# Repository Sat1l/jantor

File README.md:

# Jantor

Jantor is a split-ergo-keyboard which derives its features from other ergo keebs: [Jian](https://github.com/KGOH/Jian-Info) (extra pinky keys), [Nijuni](https://github.com/krikun98/nijuni) (copied controller footprint) and [Cantor](https://github.com/diepala/cantor) (diodeless design with a Blackpill)

## Features
* Diodeless
* <30 min assembly time
* Combined MX and Hotswap footprints
* Fully simmetrical PCB
* Two ways to connect the halves: jumper wires and TRRS

## Case

Current case design is designed to be cut out of EVA foam on a CNC laser and stacked together using EVA melting chemicals or instant glue.

Case .svg files are stored in the `case` folder, with folder `case production` having production optimised versions which have more pieces per sheet.

Raw case files are stored in `case kicad` folder in kicad project file format.

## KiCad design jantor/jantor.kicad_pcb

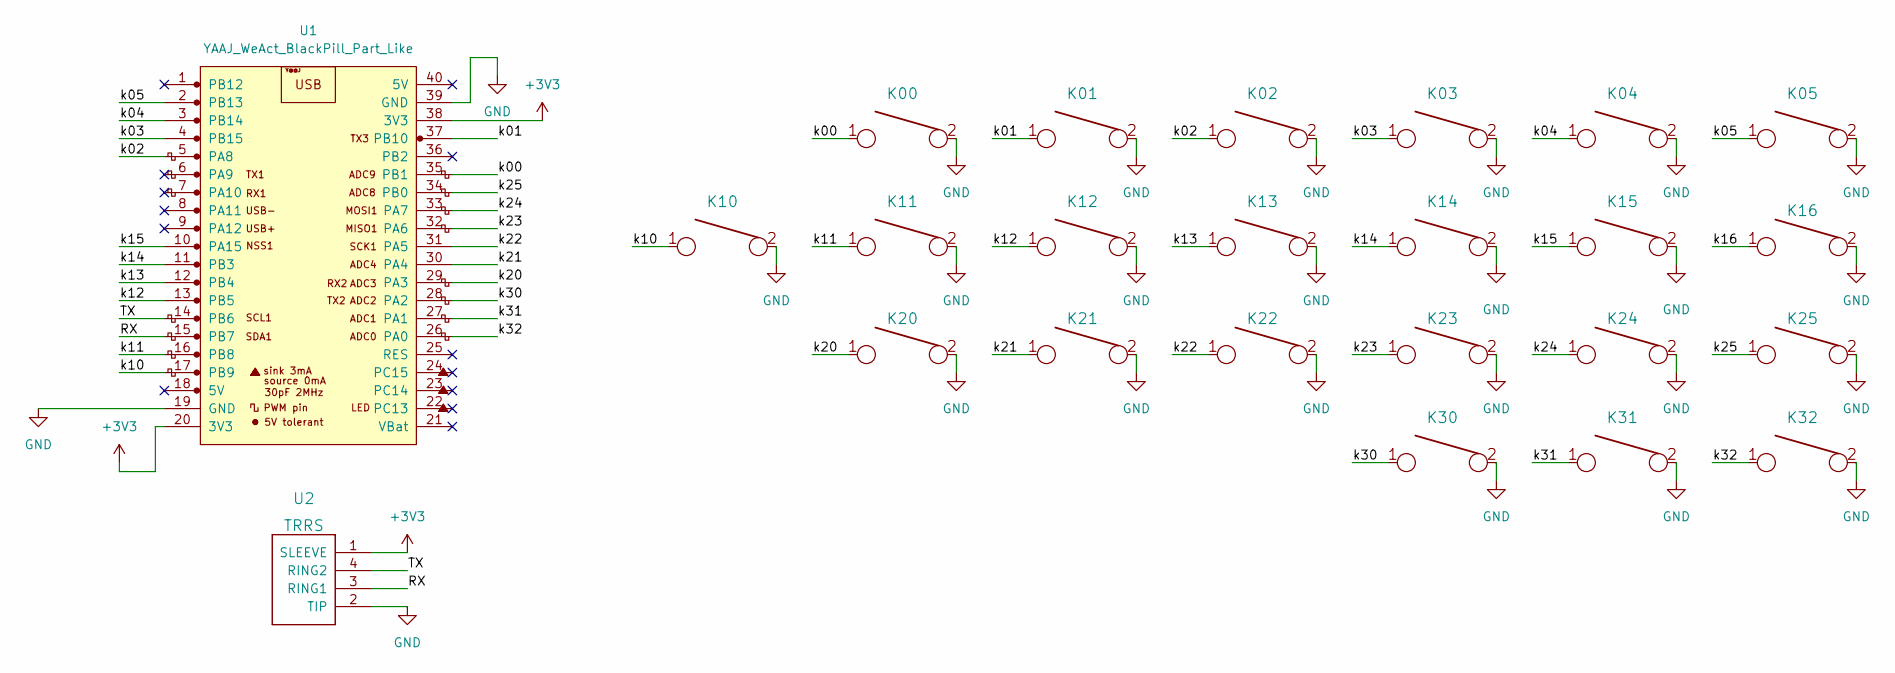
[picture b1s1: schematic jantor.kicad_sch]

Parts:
K00, K01, K02, K03, K04, K05, K10, K11, K12, K13, K14, K15, K16, K20, K21, K22, K23, K24, K25, K30, K31: KEYSW; MXOnly-1U-Hotswap-Optional-Reversible-19mm
K32: KEYSW; MXOnly-1.5U-Hotswap-Optional-Reversible-19mm
U1: YAAJ_WeAct_BlackPill_Part_Like; YAAJ_WeAct_BlackPill_2
U2: TRRS; TRRS-PJ-320A-Reversible

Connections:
+3V3: U1.20 (3V3), U1.38 (3V3), U2.1 (SLEEVE)
/RX: U1.15 (PB7), U2.3 (RING1)
/TX: U1.14 (PB6), U2.4 (RING2)
/k00: K00.1, U1.35 (PB1)
/k01: K01.1, U1.6 (PA9), U1.37 (PB10)
/k02: K02.1, U1.5 (PA8)
/k03: K03.1, U1.4 (PB15)
/k04: K04.1, U1.3 (PB14)
/k05: K05.1, U1.2 (PB13)
/k10: K10.1, U1.17 (PB9)
/k11: K11.1, U1.16 (PB8)
/k12: K12.1, U1.13 (PB5)
/k13: K13.1, U1.12 (PB4)
/k14: K14.1, U1.11 (PB3)
/k15: K15.1, U1.10 (PA15)
/k16: K16.1, U1.9 (PA12)
/k20: K20.1, U1.29 (PA3)
/k21: K21.1, U1.30 (PA4)
/k22: K22.1, U1.31 (PA5)
/k23: K23.1, U1.32 (PA6)
/k24: K24.1, U1.33 (PA7)
/k25: K25.1, U1.34 (PB0)
/k30: K30.1, U1.28 (PA2)
/k31: K31.1, U1.27 (PA1)
/k32: K32.1, U1.26 (PA0)
GND: K00.2, K01.2, K02.2, K03.2, K04.2, K05.2, K10.2, K11.2, K12.2, K13.2, K14.2, K15.2, K16.2, K20.2, K21.2, K22.2, K23.2, K24.2, K25.2, K30.2, K31.2, K32.2, U1.19 (GND), U1.39 (GND), U2.2 (TIP)

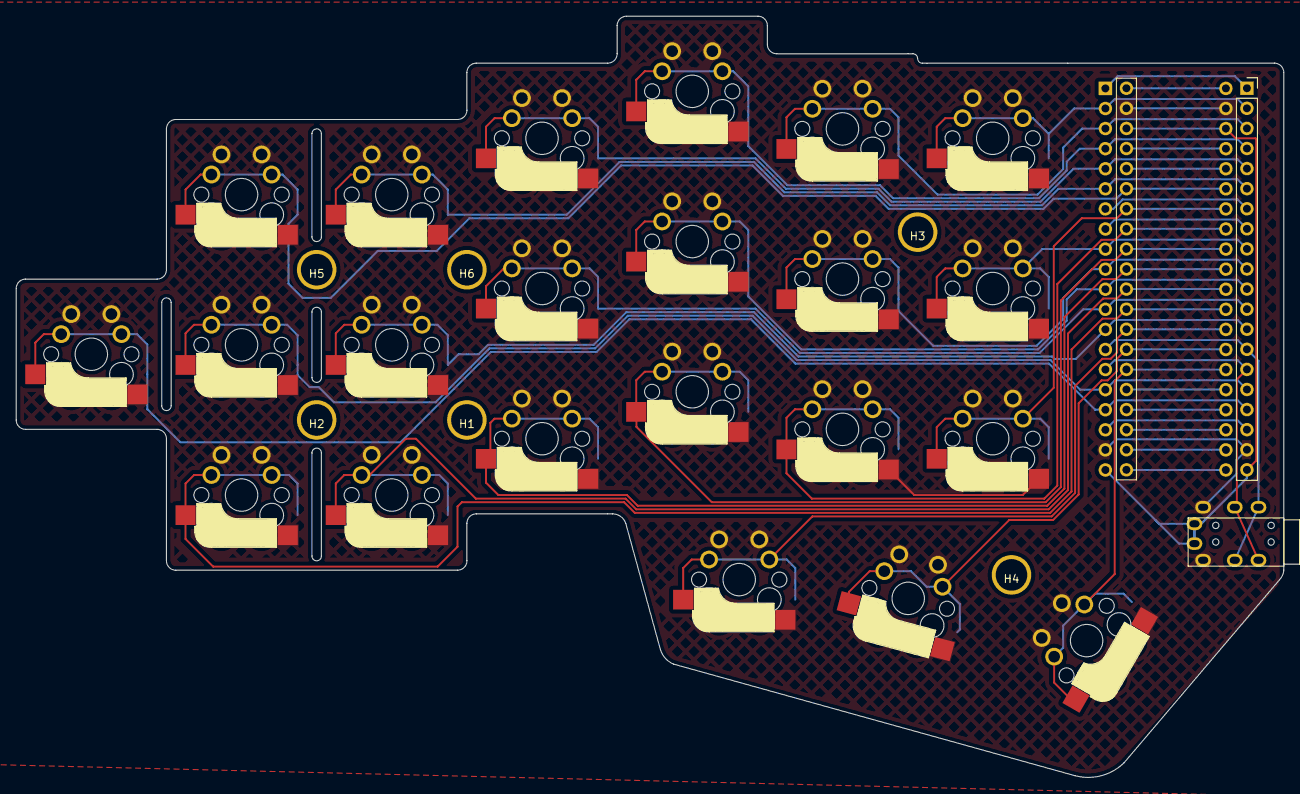
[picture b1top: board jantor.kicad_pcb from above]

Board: 2 copper layers, 160.3 x 96.3 mm, 34 parts (0 on the bottom side), 26 nets.

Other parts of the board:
B1, B3, B4: breakaway; breakaway .75U (for 19mm net)
B2: breakaway; breakaway .5U (for 19mm net)
H1, H2, H3, H4, H5, H6: MountingHole; M2_Hole_TH_Outside

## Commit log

2022-08-20 initial commit
    no wiring and edges
2022-08-21 release
2022-12-30 what i did like whaaaa
2023-06-30 proto v0.?
    Completely new pcb and a new foam case. I'm currently typing this on an assembled board.
2023-07-10 cleanup
2023-07-13 added pictures
2024-04-03 hehehe i dont remember ANYTHING
